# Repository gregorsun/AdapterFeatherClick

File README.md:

# AdapterFeatherClick

Connector between Adafruit feather Pinout (SAMD51) and Mikroelektrobika click boards

#Overview
- J1: Mikroelektronika [mikroBus](https://www.mikroe.com/mikrobus) for [Mikroelektronika click baords](https://www.mikroe.com/click)
- J2: Adafruit feather pinout [used ATAMD51 Pinout](https://learn.adafruit.com/adafruit-feather-m4-express-atsamd51/pinouts)
- J3 to J10: Additional area for soldering or connection of wires

#Adafruit Feather M4 Express with the ATSAMD51
- https://cdn-learn.adafruit.com/assets/assets/000/101/972/original/arduino_compatibles_Feather_M4_Page.png?1619812444
#Mikroelektronika mikroBus
- https://download.mikroe.com/documents/standards/mikrobus/mikrobus-standard-specification-v200.pdf

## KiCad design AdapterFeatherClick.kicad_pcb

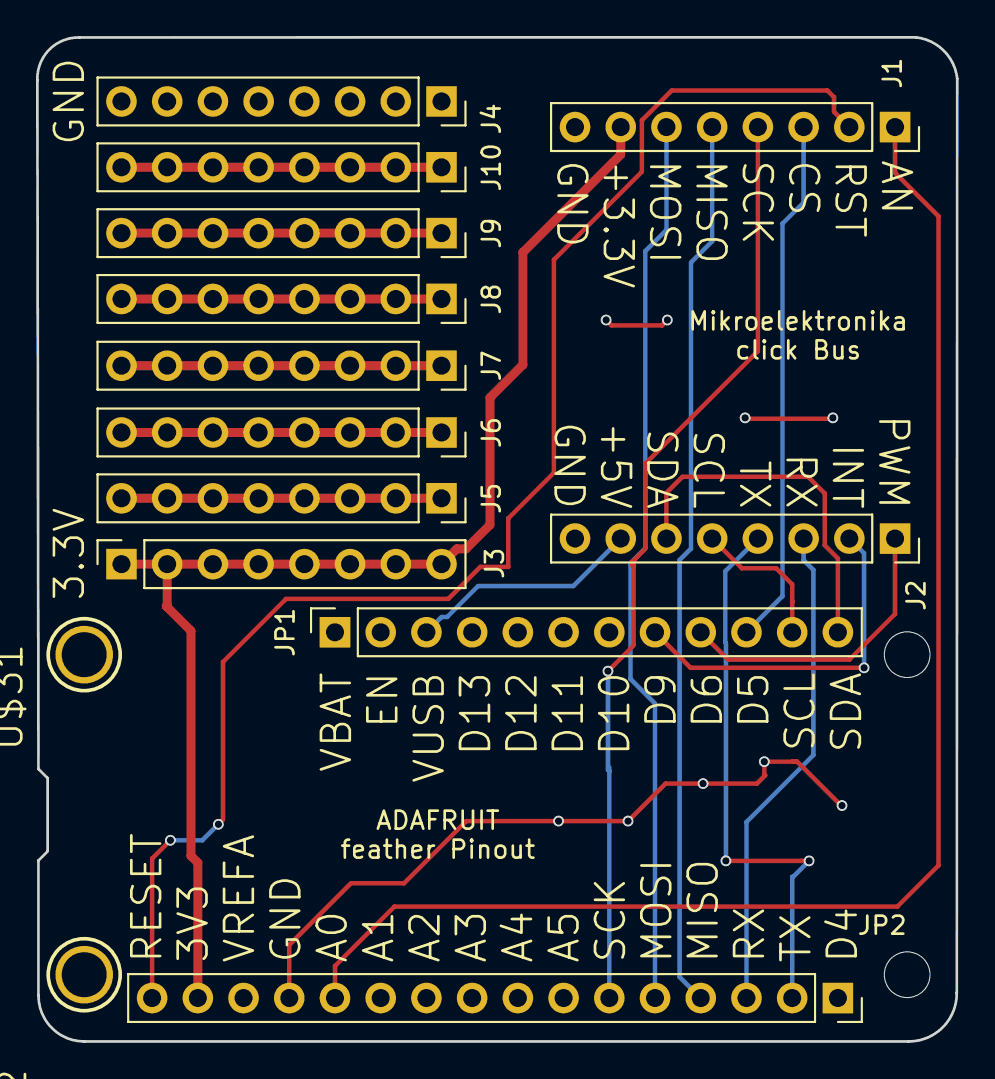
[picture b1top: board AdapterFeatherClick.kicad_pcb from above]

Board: 2 copper layers, 51.1 x 55.8 mm, 18 parts (0 on the bottom side), 21 nets.

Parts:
@HOLE0, @HOLE1: (no value)
J1, J2, J3, J4, J5, J6, J7, J8, J9, J10: Conn_01x08; PinSocket_1x08_P2.54mm_Vertical
JP1: PinSocket_1x12_P2.54mm_Vertical
JP2: PinSocket_1x16_P2.54mm_Vertical
U$5: FEATHERM4_BOT
U$6: FEATHERM4_TOP
U$31, U$32: MOUNTINGHOLE2.5; MOUNTINGHOLE_2.5_PLATED

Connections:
/+3.3V: J1.7, J3.1, J3.2, J3.3, J3.4, J3.5, J3.6, J3.7, J3.8, JP2.15
/A0: J1.1, JP2.12
/D5: J1.3, JP1.10
/D6: J2.1, JP1.9
/D9: J2.2, JP1.8
/MISO: J1.5, JP2.4
/MOSI: J1.6, JP2.5
/RX_D0: J2.3, JP2.3
/SCK: J1.4, JP2.6
/SCL: J2.5, JP1.11
/SDA: J2.6, JP1.12
/TX_D1: J2.4, JP2.2
/VBUS: J2.7, JP1.3
/~RESET: J1.2, JP2.16
GND: J1.8, J2.8, J4.1, J4.2, J4.3, J4.4, J4.5, J4.6, J4.7, J4.8, JP2.13
unnamed: J5.1, J5.2, J5.3, J5.4, J5.5, J5.6, J5.7, J5.8
unnamed: J6.1, J6.2, J6.3, J6.4, J6.5, J6.6, J6.7, J6.8
unnamed: J7.1, J7.2, J7.3, J7.4, J7.5, J7.6, J7.7, J7.8
unnamed: J8.1, J8.2, J8.3, J8.4, J8.5, J8.6, J8.7, J8.8
unnamed: J9.1, J9.2, J9.3, J9.4, J9.5, J9.6, J9.7, J9.8
unnamed: J10.1, J10.2, J10.3, J10.4, J10.5, J10.6, J10.7, J10.8

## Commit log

2021-05-07 initial version
2021-05-07 Update README.md
    initial commit
